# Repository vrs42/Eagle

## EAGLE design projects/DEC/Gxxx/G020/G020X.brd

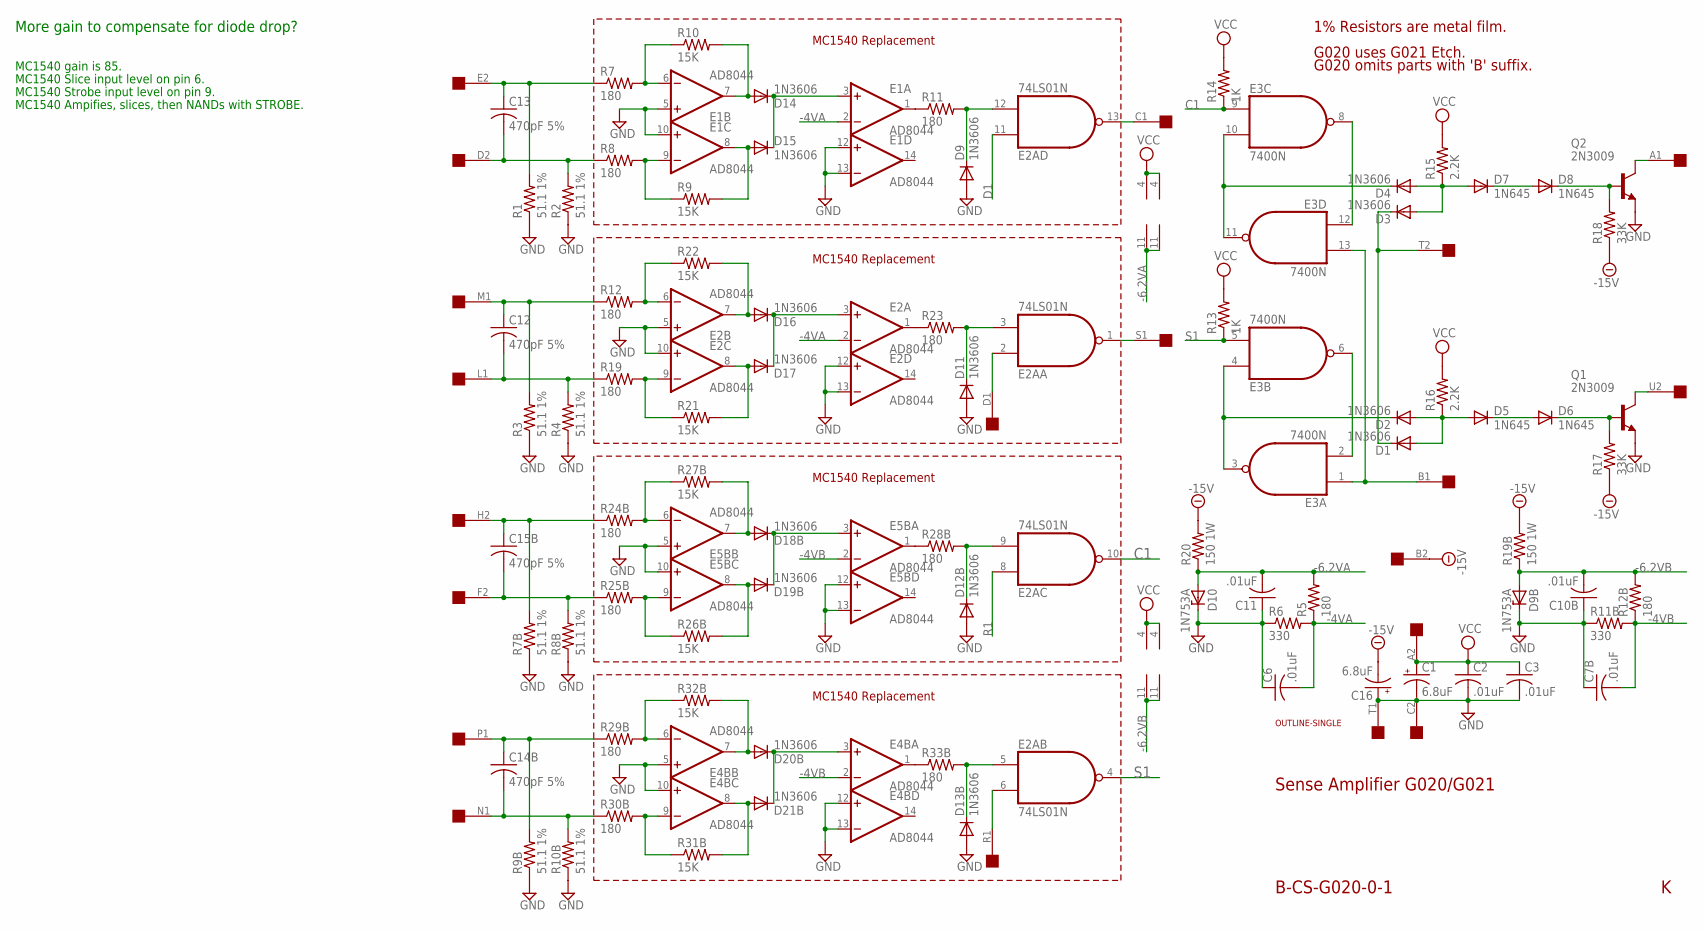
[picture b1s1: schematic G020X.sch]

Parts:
C1, C16: 6.8uF; E12-8
C2, C3, C6, C7B, C10B, C11: .01uF; C050-025X075
C12, C13, C14B, C15B: 470pF 5%; C050-025X075
D1, D2, D3, D4, D9, D11, D12B, D13B, D14, D15, D16, D17, D18B, D19B, D20B, D21B: 1N3606; DO35-10
D5, D6, D7, D8: 1N645; DO35-10
D9B, D10: 1N753A; DO35Z10
E1, E2, E4B, E5B: AD8044; DIL14
E2A: 74LS01N; DIL14
E3: 7400N; DIL14
Q1, Q2: 2N3009; TO5
R1, R2, R3, R4, R7B, R8B, R9B, R10B: 51.1 1%; 0207/10
R5, R7, R8, R11, R12, R12B, R19, R23, R24B, R25B, R28B, R29B, R30B, R33B: 180; 0207/10
R6, R11B: 330; 0207/10
R9, R10, R21, R22, R26B, R27B, R31B, R32B: 15K; 0207/10
R13, R14: 1K; 0207/10
R15, R16: 2.2K; 0207/10
R17, R18: 33K; 0207/10
R19B, R20: 150 1W; 0414/20
U$1: SINGLE; EDGE-CON2
U$2: OUTLINE-SINGLE; SINGLE

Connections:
-4VA: C6.2, E1.2 (-IN), E2.2 (-IN), R5.1, R6.2
-4VB: C7B.2, E4B.2 (-IN), E5B.2 (-IN), R11B.2, R12B.1
-6.2VA: C11.2, D10.A, E1.11 (V-), E2.11 (V-), R5.2, R20.1
-6.2VB: C10B.2, D9B.A, E4B.11 (V-), E5B.11 (V-), R12B.2, R19B.1
-15V: C16.-, R17.1, R18.1, R19B.2, R20.2, U$1.B2
A1: Q2.3 (C), U$1.A1
B1: E3.1 (I0), E3.13 (I1), U$1.B1
C1: E2A.10 (O), E2A.13 (O), E3.9 (I0), R14.1, U$1.C1
D1: E2A.2 (I0), E2A.11 (I0), U$1.D1
D2: C13.2, R2.2, R8.1, U$1.D2
E2: C13.1, R1.2, R7.1, U$1.E2
F2: C15B.2, R8B.2, R25B.1, U$1.F2
GND: C1.-, C2.2, C3.2, C6.1, C7B.1, C10B.1, C11.1, C16.+, D9.A, D9B.C, D10.C, D11.A, D12B.A, D13B.A, E1.5 (+IN), E1.10 (+IN), E1.12 (+IN), E1.13 (-IN), E2.5 (+IN), E2.10 (+IN), E2.12 (+IN), E2.13 (-IN), E2A.7 (GND), E3.7 (GND), E4B.5 (+IN), E4B.10 (+IN), E4B.12 (+IN), E4B.13 (-IN), E5B.5 (+IN), E5B.10 (+IN), E5B.12 (+IN), E5B.13 (-IN), Q1.1 (E), Q2.1 (E), R1.1, R2.1, R3.1, R4.1, R6.1, R7B.1, R8B.1, R9B.1, R10B.1, R11B.1, U$1.C2, U$1.T1
H2: C15B.1, R7B.2, R24B.1, U$1.H2
L1: C12.2, R4.2, R19.1, U$1.L1
M1: C12.1, R3.2, R12.1, U$1.M1
N1: C14B.2, R10B.2, R30B.1, U$1.N1
unnamed: D20B.C, D21B.C, E4B.3 (+IN)
unnamed: D18B.C, D19B.C, E5B.3 (+IN)
unnamed: E3.8 (O), E3.12 (I0)
unnamed: D1.A, D2.A, D5.A, R16.1
unnamed: D4.C, E3.10 (I1), E3.11 (O)
unnamed: D2.C, E3.3 (O), E3.4 (I0)
unnamed: E3.2 (I1), E3.6 (O)
unnamed: D3.A, D4.A, D7.A, R15.1
unnamed: D7.C, D8.A
unnamed: D5.C, D6.A
unnamed: D8.C, Q2.2 (B), R18.2
unnamed: D6.C, Q1.2 (B), R17.2
unnamed: E1.6 (-IN), R7.2, R10.1
unnamed: E1.9 (-IN), R8.2, R9.1
unnamed: D14.C, D15.C, E1.3 (+IN)
unnamed: E1.1 (OUT), R11.1
unnamed: D9.C, E2A.12 (I1), R11.2
unnamed: D15.A, E1.8 (OUT), R9.2
unnamed: E2.6 (-IN), R12.2, R22.1
unnamed: E2.9 (-IN), R19.2, R21.1
unnamed: D16.A, E2.7 (OUT), R22.2
unnamed: E2.1 (OUT), R23.1
unnamed: D11.C, E2A.3 (I1), R23.2
unnamed: E5B.6 (-IN), R24B.2, R27B.1
unnamed: E5B.9 (-IN), R25B.2, R26B.1
unnamed: D18B.A, E5B.7 (OUT), R27B.2
unnamed: D14.A, E1.7 (OUT), R10.2
unnamed: E5B.1 (OUT), R28B.1
unnamed: D12B.C, E2A.9 (I1), R28B.2
unnamed: D17.A, E2.8 (OUT), R21.2
unnamed: E4B.6 (-IN), R29B.2, R32B.1
unnamed: D19B.A, E5B.8 (OUT), R26B.2
unnamed: D20B.A, E4B.7 (OUT), R32B.2
unnamed: E4B.1 (OUT), R33B.1
unnamed: E4B.9 (-IN), R30B.2, R31B.1
unnamed: D13B.C, E2A.5 (I0), R33B.2
unnamed: D16.C, D17.C, E2.3 (+IN)
unnamed: D21B.A, E4B.8 (OUT), R31B.2
P1: C14B.1, R9B.2, R29B.1, U$1.P1
R1: E2A.6 (I1), E2A.8 (I0), U$1.R1
S1: E2A.1 (O), E2A.4 (O), E3.5 (I1), R13.1, U$1.S1
T2: D1.C, D3.C, U$1.T2
U2: Q1.3 (C), U$1.U2
VCC: C1.+, C2.1, C3.1, E1.4 (V+), E2.4 (V+), E2A.14 (VCC), E3.14 (VCC), E4B.4 (V+), E5B.4 (V+), R13.2, R14.2, R15.2, R16.2, U$1.A2

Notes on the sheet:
MC1540 gain is 85.
MC1540 Slice input level on pin 6.
MC1540 Strobe input level on pin 9.
MC1540 Ampifies, slices, then NANDs with STROBE.
Sense Amplifier G020/G021
B-CS-G020-0-1
G020 omits parts with 'B' suffix.
G020 uses G021 Etch.
MC1540 Replacement
1% Resistors are metal film.
More gain to compensate for diode drop?

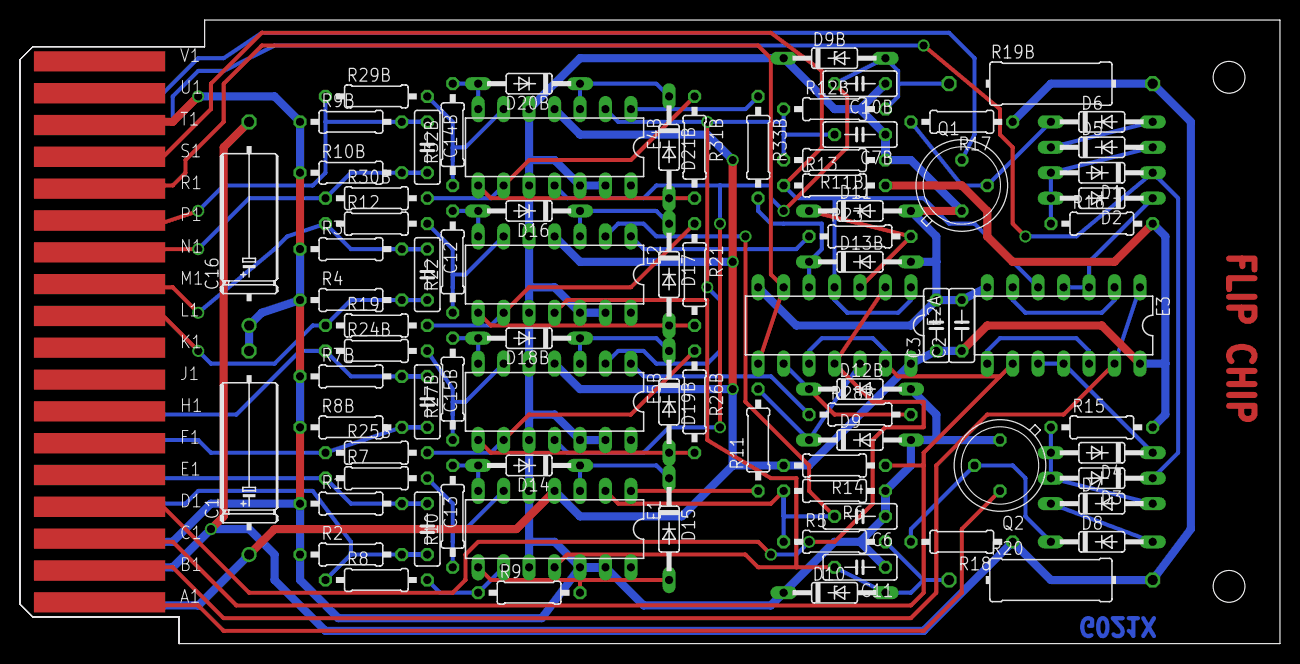
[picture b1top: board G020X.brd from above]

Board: 3 copper layers, 125.7 x 62.2 mm, 84 parts (0 on the bottom side), 61 nets.

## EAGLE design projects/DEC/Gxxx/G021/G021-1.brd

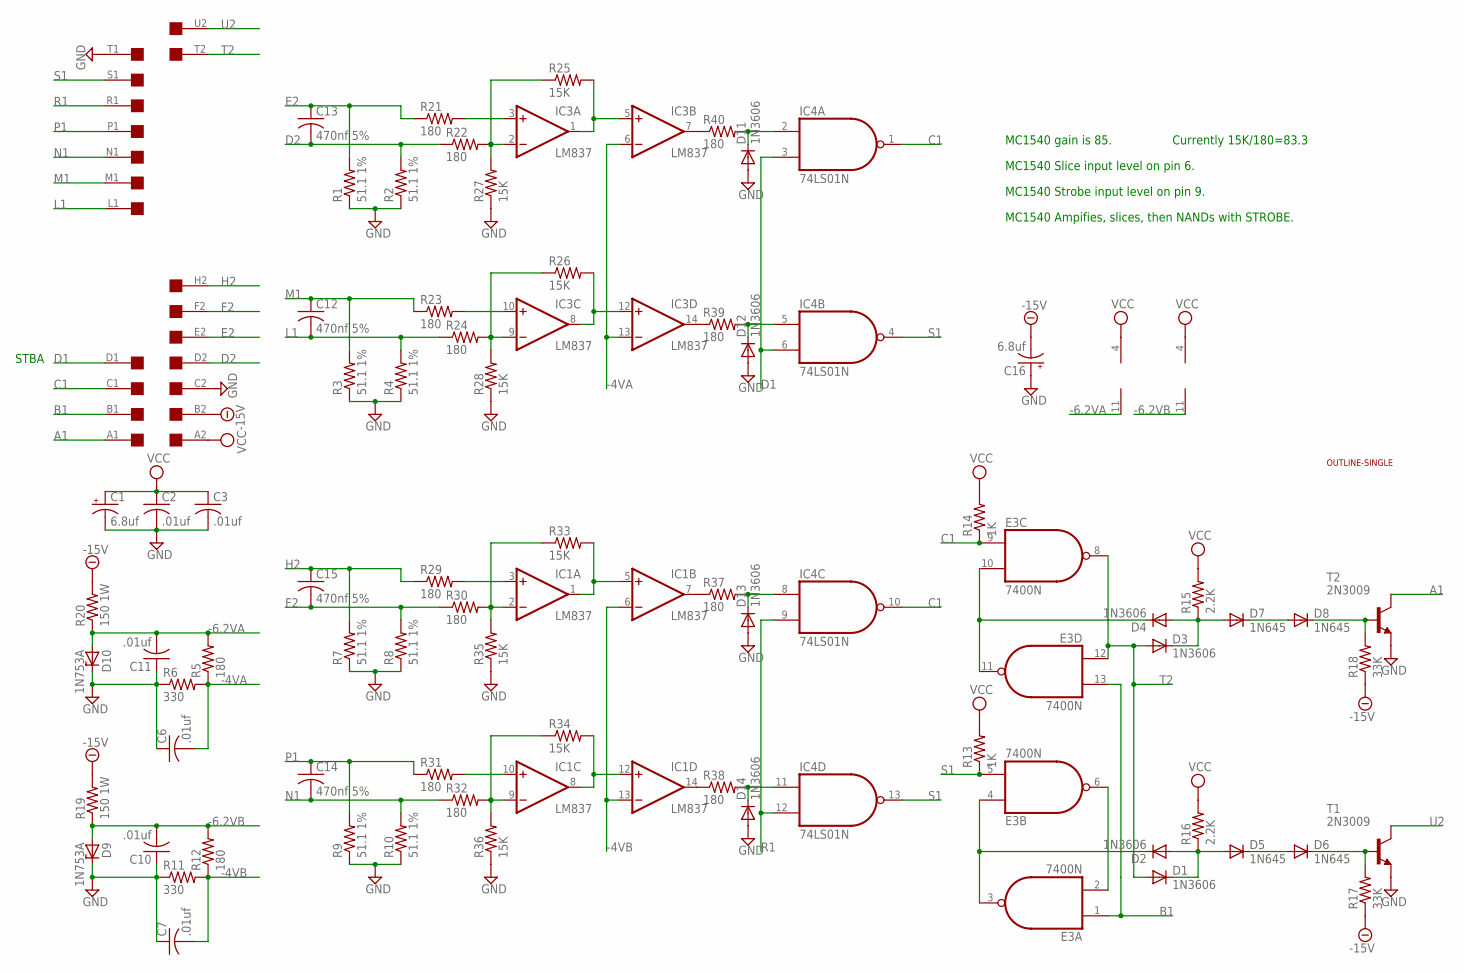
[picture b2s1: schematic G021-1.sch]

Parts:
C1, C16: 6.8uf; E15-5
C2, C3, C6, C7, C10, C11: .01uf; C050-025X075
C12, C13, C14, C15: 470nf 5%; C050-025X075
D1, D2, D3, D4, D11, D12, D13, D14: 1N3606; DO35-10
D5, D6, D7, D8: 1N645; DO35-10
D9, D10: 1N753A; F126Z10
E3: 7400N; DIL14
IC1, IC3: LM837; DIL14
IC4: 74LS01N; DIL14
R1, R2, R3, R4, R7, R8, R9, R10: 51.1 1%; 0207/10
R5, R12, R21, R22, R23, R24, R29, R30, R31, R32, R37, R38, R39, R40: 180; 0207/10
R6, R11: 330; 0207/10
R13, R14: 1K; 0207/10
R15, R16: 2.2K; 0207/10
R17, R18: 33K; 0207/10
R19, R20: 150 1W; 0414/15
R25, R26, R27, R28, R33, R34, R35, R36: 15K; 0207/10
T1, T2: 2N3009; TO92
U$1: SINGLE; EDGE-CON2
U$2: OUTLINE-SINGLE; SINGLE

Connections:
-4VA: C6.2, IC3.6 (-IN), IC3.13 (-IN), R5.1, R6.2
-4VB: C7.2, IC1.6 (-IN), IC1.13 (-IN), R11.2, R12.1
-6.2VA: C11.2, D10.A, IC3.11 (V-), R5.2, R20.1
-6.2VB: C10.2, D9.A, IC1.11 (V-), R12.2, R19.1
-15V: C16.-, R17.1, R18.1, R19.2, R20.2, U$1.B2
A1: T2.1 (C), U$1.A1
B1: E3.1 (I0), E3.13 (I1), U$1.B1
C1: E3.9 (I0), IC4.1 (O), IC4.10 (O), R14.1, U$1.C1
D1: IC4.3 (I1), IC4.6 (I1), U$1.D1
D2: C13.2, R2.2, R22.1, U$1.D2
E2: C13.1, R1.2, R21.1, U$1.E2
F2: C15.2, R8.2, R30.1, U$1.F2
GND: C1.-, C2.2, C3.2, C6.1, C7.1, C10.1, C11.1, C16.+, D9.C, D10.C, D11.A, D12.A, D13.A, D14.A, E3.7 (GND), IC4.7 (GND), R1.1, R2.1, R3.1, R4.1, R6.1, R7.1, R8.1, R9.1, R10.1, R11.1, R27.1, R28.1, R35.1, R36.1, T1.3 (E), T2.3 (E), U$1.C2, U$1.T1
H2: C15.1, R7.2, R29.1, U$1.H2
L1: C12.2, R4.2, R24.1, U$1.L1
M1: C12.1, R3.2, R23.1, U$1.M1
N1: C14.2, R10.2, R32.1, U$1.N1
unnamed: IC3.7 (OUT), R40.1
unnamed: IC3.14 (OUT), R39.1
unnamed: IC1.7 (OUT), R37.1
unnamed: IC1.14 (OUT), R38.1
unnamed: IC3.8 (OUT), IC3.12 (+IN), R26.2
unnamed: D1.C, D2.A, D5.A, R16.1
unnamed: D4.C, E3.10 (I1), E3.11 (O)
unnamed: D2.C, E3.3 (O), E3.4 (I0)
unnamed: E3.2 (I1), E3.6 (O)
unnamed: D3.C, D4.A, D7.A, R15.1
unnamed: D7.C, D8.A
unnamed: D5.C, D6.A
unnamed: D8.C, R18.2, T2.2 (B)
unnamed: D6.C, R17.2, T1.2 (B)
unnamed: IC3.1 (OUT), IC3.5 (+IN), R25.2
unnamed: IC3.9 (-IN), R24.2, R26.1, R28.2
unnamed: IC3.10 (+IN), R23.2
unnamed: IC3.2 (-IN), R22.2, R25.1, R27.2
unnamed: IC3.3 (+IN), R21.2
unnamed: IC1.8 (OUT), IC1.12 (+IN), R34.2
unnamed: IC1.1 (OUT), IC1.5 (+IN), R33.2
unnamed: IC1.9 (-IN), R32.2, R34.1, R36.2
unnamed: IC1.10 (+IN), R31.2
unnamed: IC1.2 (-IN), R30.2, R33.1, R35.2
unnamed: IC1.3 (+IN), R29.2
unnamed: D11.C, IC4.2 (I0), R40.2
unnamed: D12.C, IC4.5 (I0), R39.2
unnamed: D14.C, IC4.11 (I0), R38.2
unnamed: D13.C, IC4.8 (I0), R37.2
P1: C14.1, R9.2, R31.1, U$1.P1
R1: IC4.9 (I1), IC4.12 (I1), U$1.R1
S1: E3.5 (I1), IC4.4 (O), IC4.13 (O), R13.1, U$1.S1
T2: D1.A, D3.A, E3.8 (O), E3.12 (I0), U$1.T2
U2: T1.1 (C), U$1.U2
VCC: C1.+, C2.1, C3.1, E3.14 (VCC), IC1.4 (V+), IC3.4 (V+), IC4.14 (VCC), R13.2, R14.2, R15.2, R16.2, U$1.A2

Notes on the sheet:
STBA
MC1540 gain is 85.
MC1540 Slice input level on pin 6.
MC1540 Strobe input level on pin 9.
MC1540 Ampifies, slices, then NANDs with STROBE.
Currently 15K/180=83.3

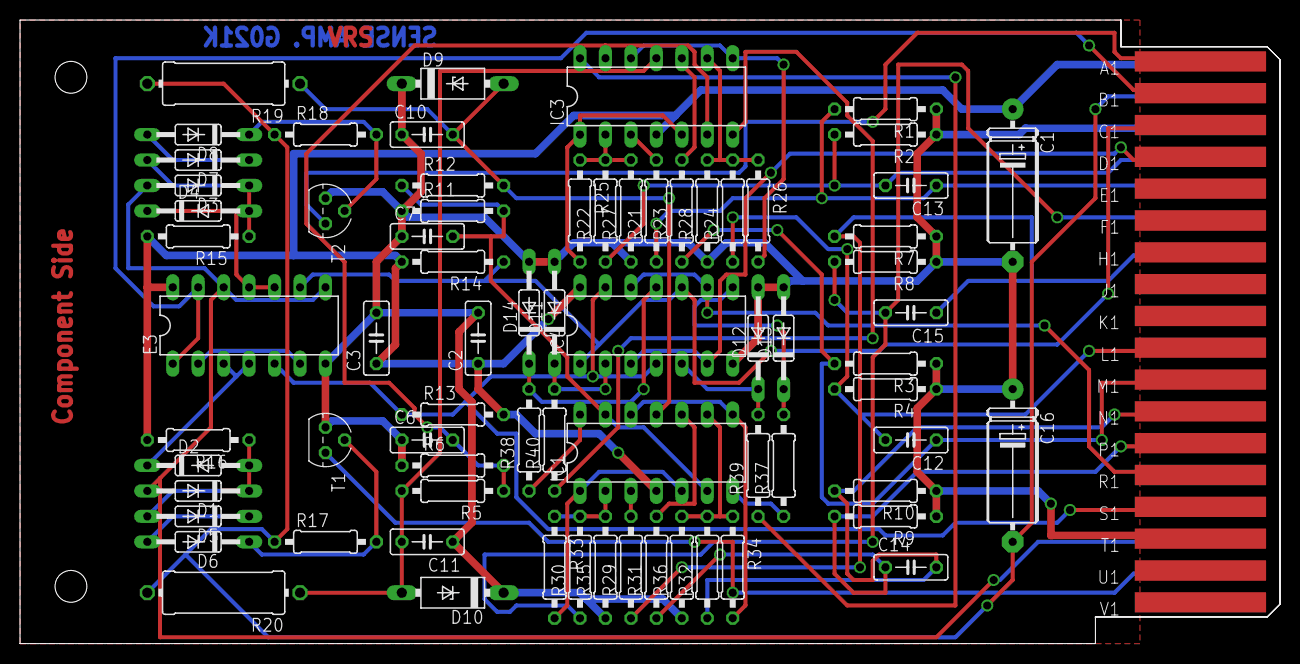
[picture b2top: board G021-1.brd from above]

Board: 2 copper layers, 125.7 x 62.2 mm, 74 parts (0 on the bottom side), 52 nets.

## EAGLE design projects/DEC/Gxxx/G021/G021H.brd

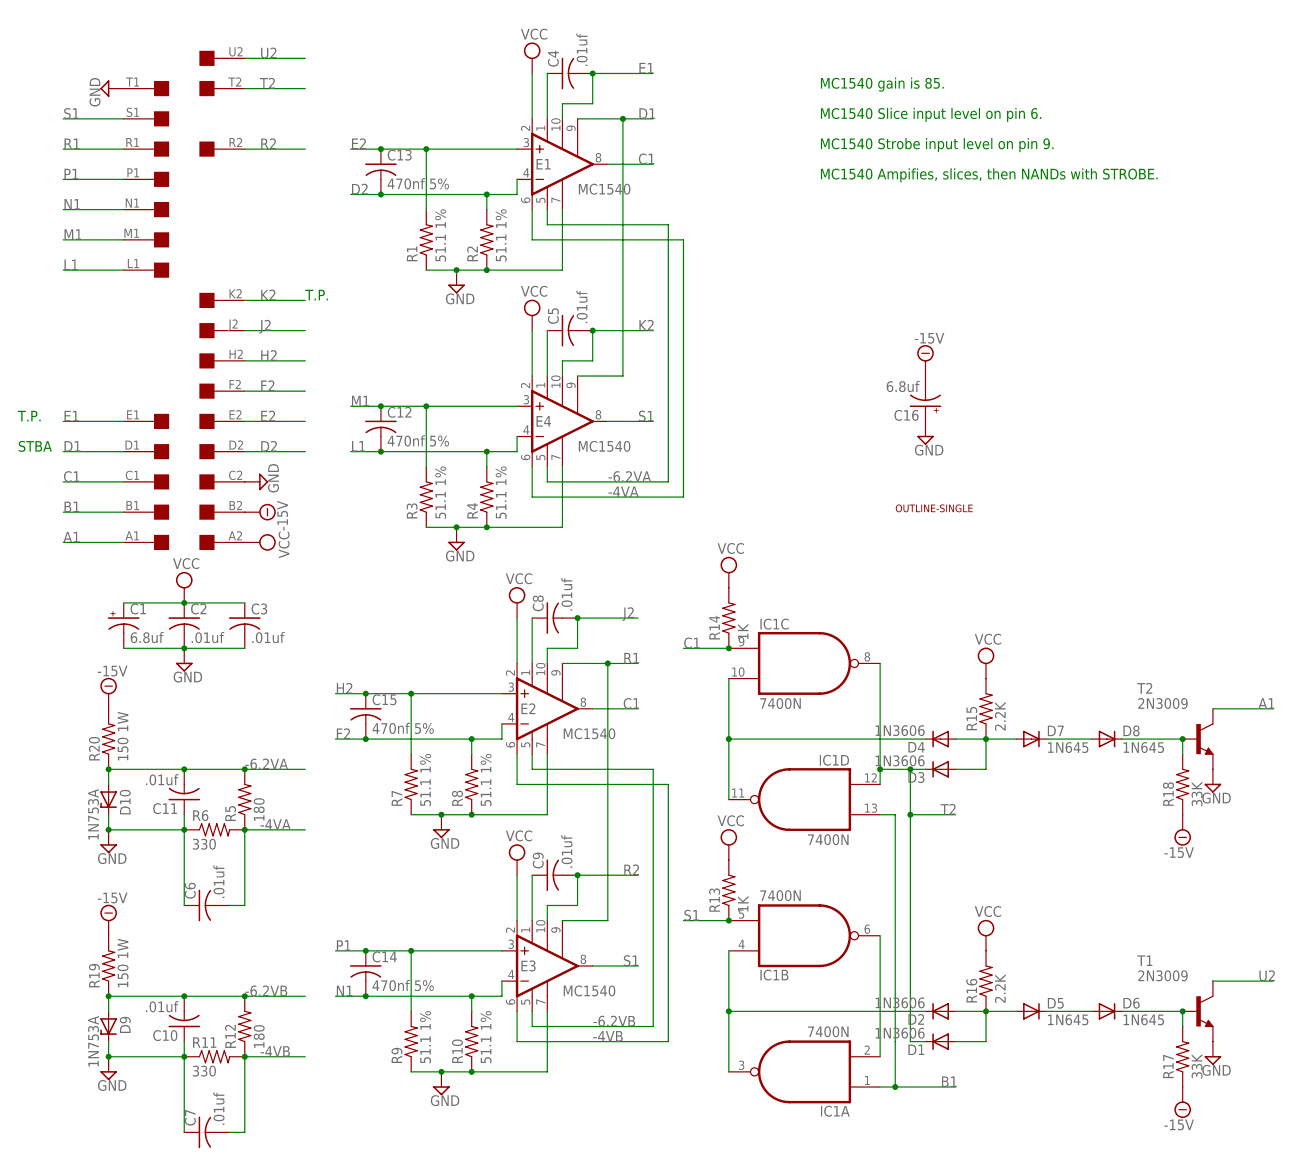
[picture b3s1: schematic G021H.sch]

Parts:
C1, C16: 6.8uf; E22-6
C2, C3, C4, C5, C6, C7, C8, C9, C10, C11: .01uf; C050-025X075
C12, C13, C14, C15: 470nf 5%; C050-025X075
D1, D2, D3, D4: 1N3606; DO35-10
D5, D6, D7, D8: 1N645; DO35-10
D9, D10: 1N753A; F126Z10
E1, E2, E3, E4: MC1540; 602B
IC1: 7400N; DIL14
R1, R2, R3, R4, R7, R8, R9, R10: 51.1 1%; 0207/10
R5, R12: 180; 0207/10
R6, R11: 330; 0207/10
R13, R14: 1K; 0207/10
R15, R16: 2.2K; 0207/10
R17, R18: 33K; 0207/10
R19, R20: 150 1W; 0414/15
T1, T2: 2N3009; TO92
U$1: SINGLE; EDGE-CON2
U$2: OUTLINE-SINGLE; SINGLE

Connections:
-4VA: C6.2, E1.6 (SLICE), E4.6 (SLICE), R5.1, R6.2
-4VB: C7.2, E2.6 (SLICE), E3.6 (SLICE), R11.2, R12.1
-6.2VA: C11.2, D10.A, E1.5 (V-), E4.5 (V-), R5.2, R20.1
-6.2VB: C10.2, D9.A, E2.5 (V-), E3.5 (V-), R12.2, R19.1
-15V: C16.-, R17.1, R18.1, R19.2, R20.2, U$1.B2
A1: T2.1 (C), U$1.A1
B1: IC1.1 (I0), IC1.13 (I1), U$1.B1
C1: E1.8 (OUT), E2.8 (OUT), IC1.9 (I0), R14.1, U$1.C1
D1: E1.9 (ISTROBE), E4.9 (ISTROBE), U$1.D1
D2: C13.2, E1.4 (-IN), R2.2, U$1.D2
E1: C4.2, E1.10 (CEXTB), U$1.E1
E2: C13.1, E1.3 (+IN), R1.2, U$1.E2
F2: C15.2, E2.4 (-IN), R8.2, U$1.F2
GND: C1.-, C2.2, C3.2, C6.1, C7.1, C10.1, C11.1, C16.+, D9.C, D10.C, E1.7 (GND), E2.7 (GND), E3.7 (GND), E4.7 (GND), IC1.7 (GND), R1.1, R2.1, R3.1, R4.1, R6.1, R7.1, R8.1, R9.1, R10.1, R11.1, T1.3 (E), T2.3 (E), U$1.C2, U$1.T1
H2: C15.1, E2.3 (+IN), R7.2, U$1.H2
J2: C8.2, E2.10 (CEXTB), U$1.J2
K2: C5.2, E4.10 (CEXTB), U$1.K2
L1: C12.2, E4.4 (-IN), R4.2, U$1.L1
M1: C12.1, E4.3 (+IN), R3.2, U$1.M1
N1: C14.2, E3.4 (-IN), R10.2, U$1.N1
unnamed: C4.1, E1.1 (CEXTA)
unnamed: C8.1, E2.1 (CEXTA)
unnamed: C5.1, E4.1 (CEXTA)
unnamed: C9.1, E3.1 (CEXTA)
unnamed: D1.A, D2.A, D5.A, R16.1
unnamed: D4.C, IC1.10 (I1), IC1.11 (O)
unnamed: D2.C, IC1.3 (O), IC1.4 (I0)
unnamed: IC1.2 (I1), IC1.6 (O)
unnamed: D3.A, D4.A, D7.A, R15.1
unnamed: D7.C, D8.A
unnamed: D5.C, D6.A
unnamed: D8.C, R18.2, T2.2 (B)
unnamed: D6.C, R17.2, T1.2 (B)
P1: C14.1, E3.3 (+IN), R9.2, U$1.P1
R1: E2.9 (ISTROBE), E3.9 (ISTROBE), U$1.R1
R2: C9.2, E3.10 (CEXTB), U$1.R2
S1: E3.8 (OUT), E4.8 (OUT), IC1.5 (I1), R13.1, U$1.S1
T2: D1.C, D3.C, IC1.8 (O), IC1.12 (I0), U$1.T2
U2: T1.1 (C), U$1.U2
VCC: C1.+, C2.1, C3.1, E1.2 (V+), E2.2 (V+), E3.2 (V+), E4.2 (V+), IC1.14 (VCC), R13.2, R14.2, R15.2, R16.2, U$1.A2

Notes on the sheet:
T.P.
STBA
MC1540 gain is 85.
MC1540 Slice input level on pin 6.
MC1540 Strobe input level on pin 9.
MC1540 Ampifies, slices, then NANDs with STROBE.

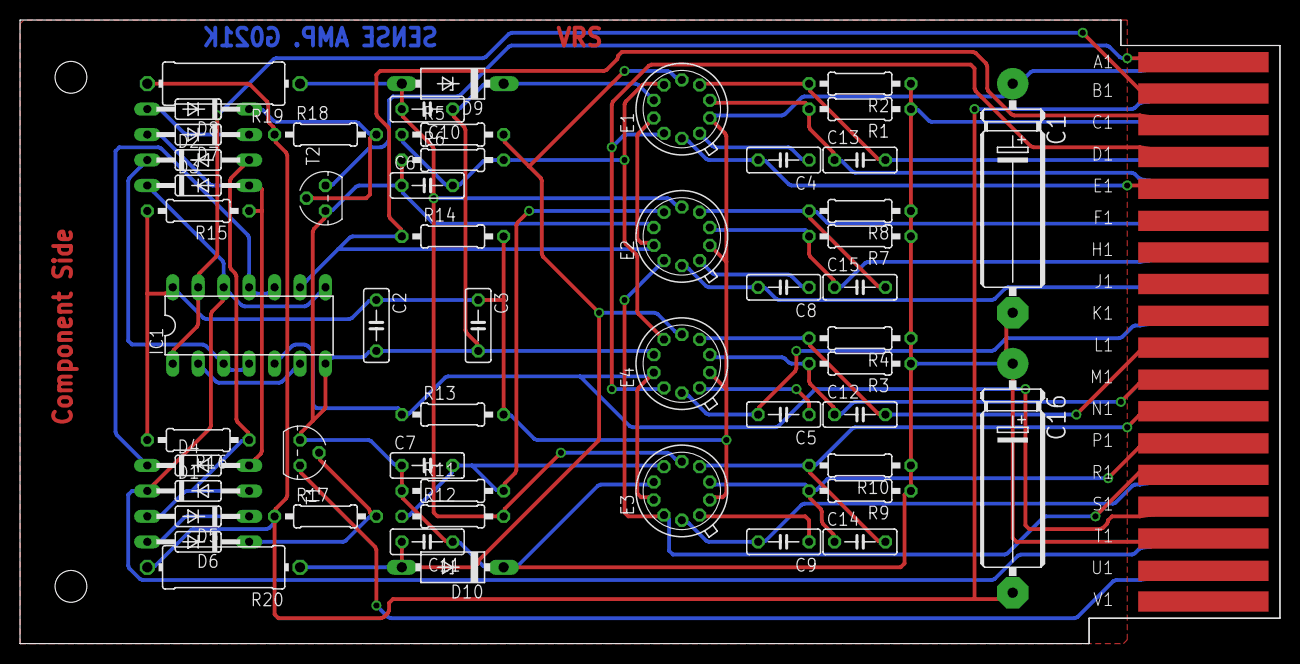
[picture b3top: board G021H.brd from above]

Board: 2 copper layers, 125.7 x 62.2 mm, 55 parts (0 on the bottom side), 40 nets.
